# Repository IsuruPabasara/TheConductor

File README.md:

The instrument is designed to help stroke patients in their recovery journey. 
It is meant to be used as a motivation to move their impaied arm in certain directions and angles.
The music comming from the device will be useful to the user themselves as well as the physical therapist guiding the process.

Demo can be found at https://youtu.be/o3slCzBoATE

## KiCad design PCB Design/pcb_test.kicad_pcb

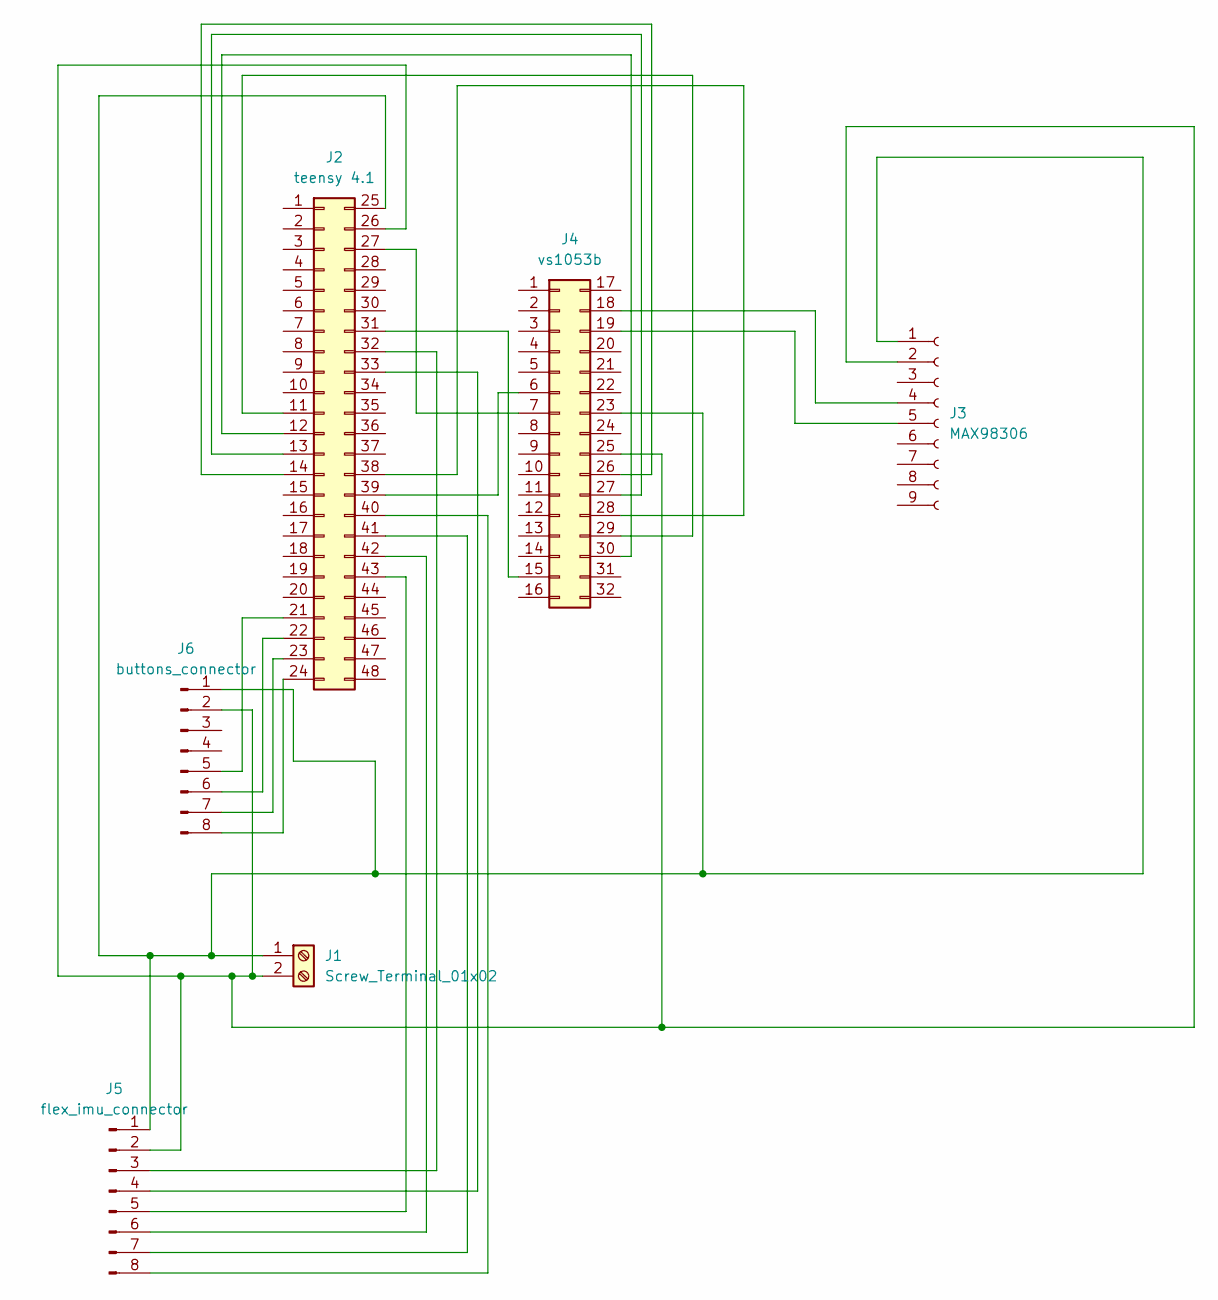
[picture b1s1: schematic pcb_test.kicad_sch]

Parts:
J1: Screw_Terminal_01x02; PhoenixContact_MCV_1,5_2-G-3.5_1x02_P3.50mm_Vertical
J2: teensy 4.1; teensy4.1
J3: MAX98306; PinSocket_1x09_P2.54mm_Vertical
J4: vs1053b; vs1053b_2
J5: flex_imu_connector; PinHeader_2x04_P2.54mm_Vertical
J6: buttons_connector; PinHeader_2x04_P2.54mm_Vertical

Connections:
unnamed: J1.1, J2.25, J3.1, J4.23, J5.1, J6.1
unnamed: J1.2, J2.26, J3.2, J4.25, J5.2, J6.2
unnamed: J2.11, J4.29
unnamed: J2.12, J4.30
unnamed: J2.13, J4.27
unnamed: J2.14, J4.26
unnamed: J2.21, J6.5
unnamed: J2.22, J6.6
unnamed: J2.23, J6.7
unnamed: J2.24, J6.8
unnamed: J2.27, J4.7
unnamed: J2.31, J4.15
unnamed: J2.32, J5.3
unnamed: J2.33, J5.4
unnamed: J2.38, J4.28
unnamed: J2.39, J4.6
unnamed: J2.40, J5.8
unnamed: J2.41, J5.7
unnamed: J2.42, J5.6
unnamed: J2.43, J5.5
unnamed: J3.4, J4.18
unnamed: J3.5, J4.19

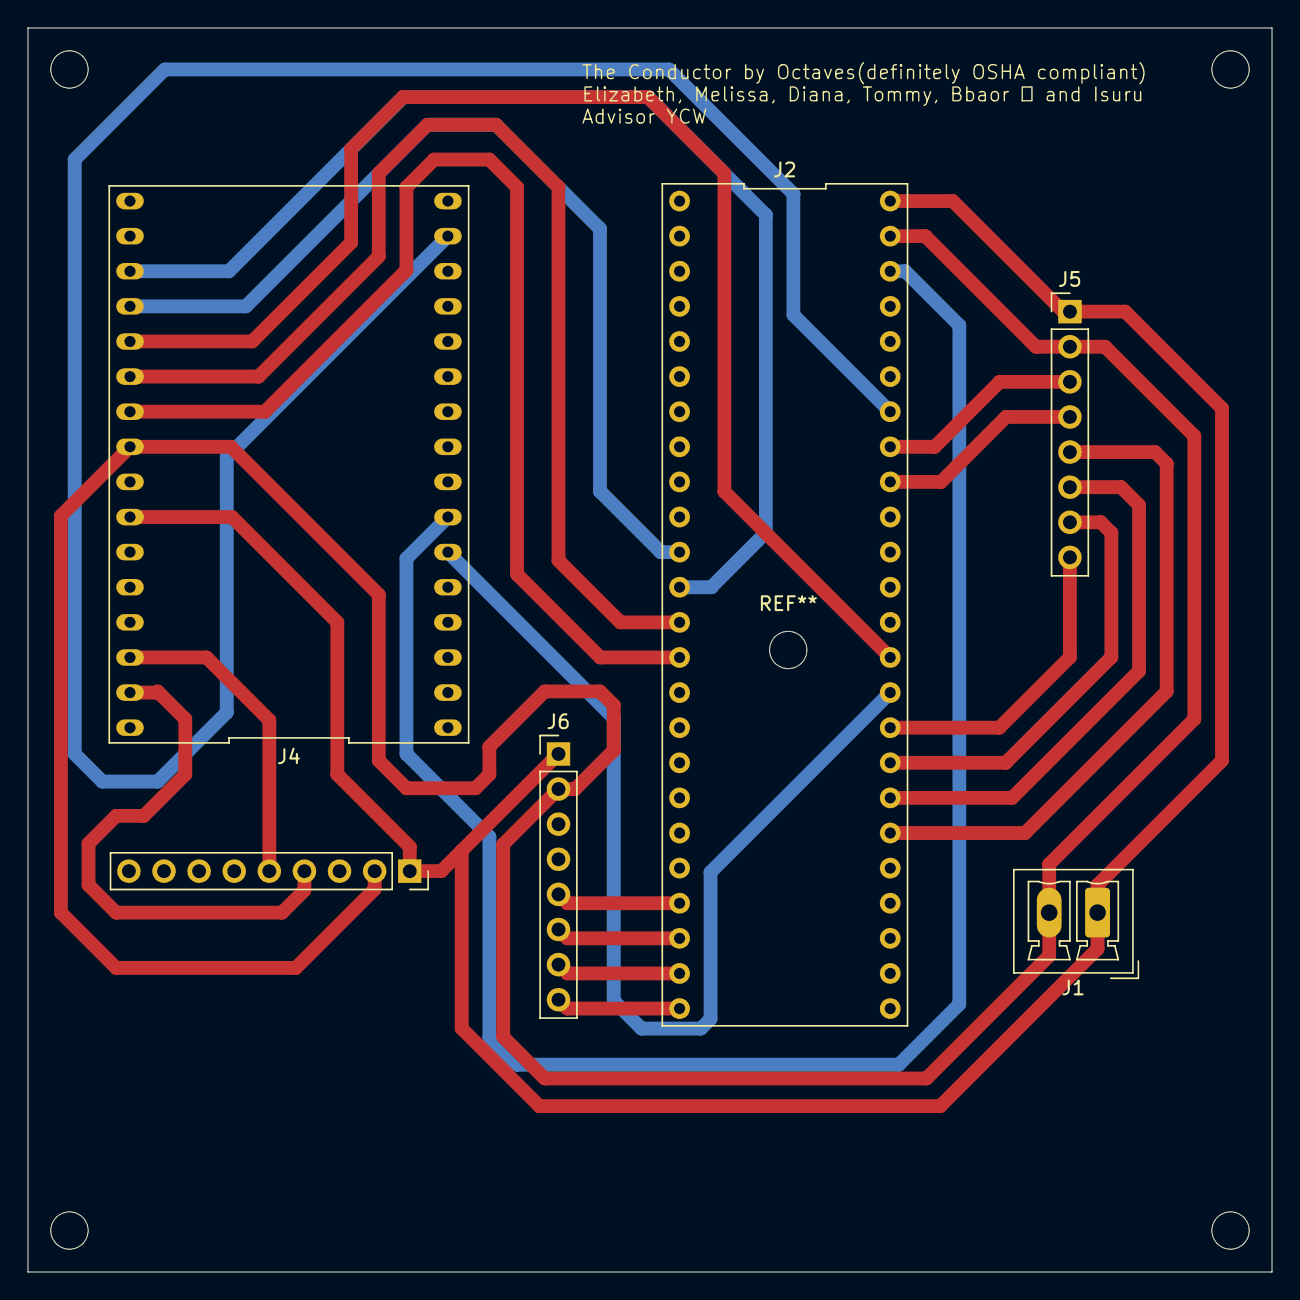
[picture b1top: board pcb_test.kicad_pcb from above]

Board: 2 copper layers, 90.0 x 90.0 mm, 6 parts (0 on the bottom side), 22 nets.

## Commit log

2024-09-09 second commit
2024-09-09 remove vid
2024-09-18 All material
2024-09-18 Setup image
2025-07-09 Schematic png add
